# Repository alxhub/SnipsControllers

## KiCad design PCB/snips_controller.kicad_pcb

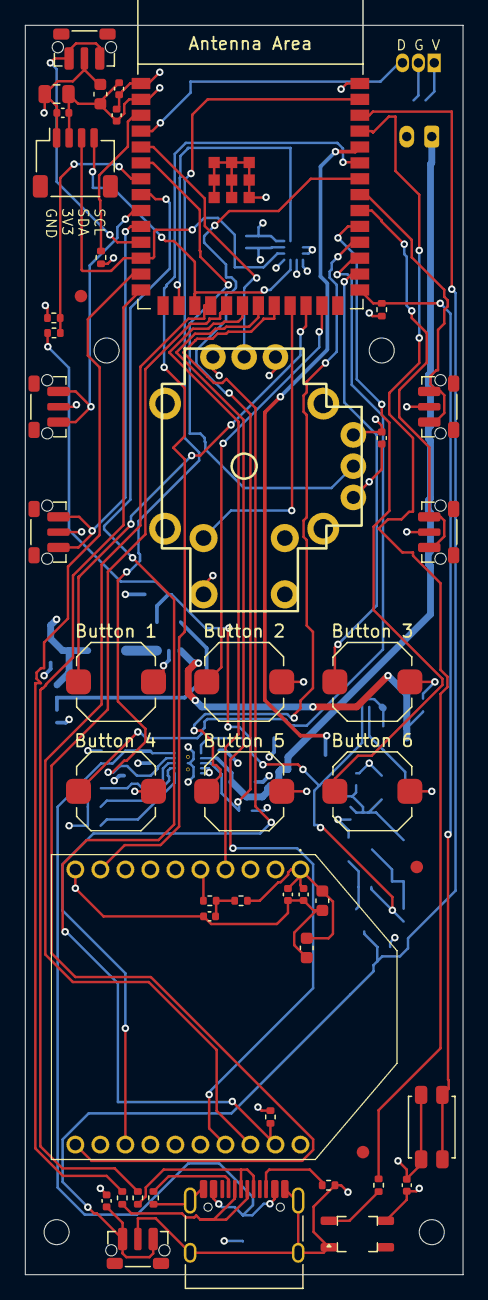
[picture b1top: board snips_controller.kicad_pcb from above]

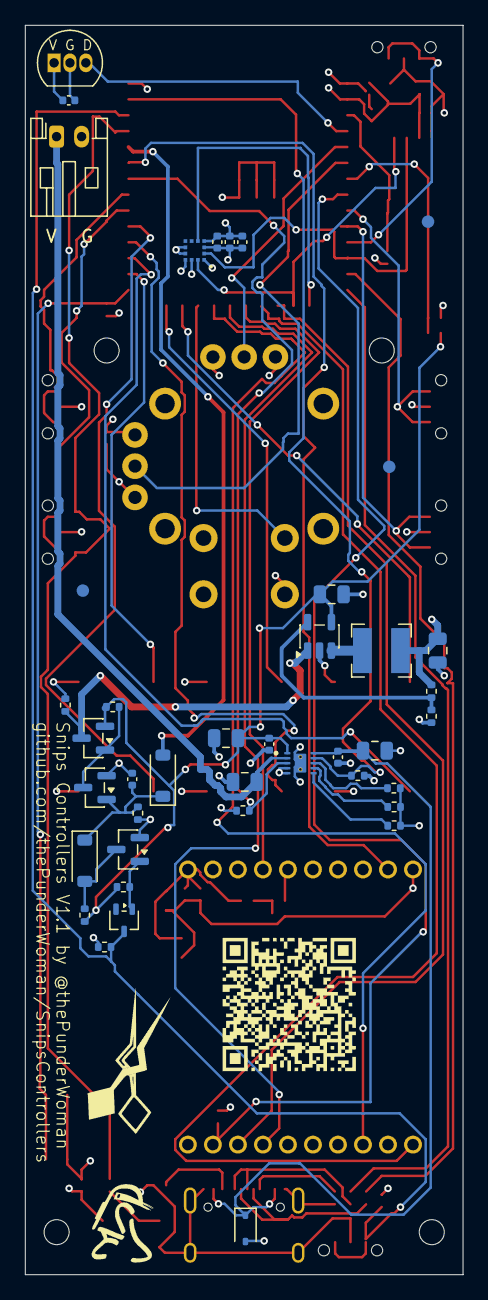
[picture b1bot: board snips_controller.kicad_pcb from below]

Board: 4 copper layers, 35.0 x 99.9 mm, 95 parts (44 on the bottom side), 57 nets.

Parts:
BT1: PH 2-pin battery RIGHT-ANGLE HORIZONTAL; JST_PH_S2B-PH-K_1x02_P2.00mm_Horizontal
C_3V3_1: 10µF; C_0603_1608Metric
C_3V3_2: 100nF; C_0402_1005Metric
C_3V3_3: 39pF; C_0402_1005Metric
C_ACCEL_1: 10nF; C_0402_1005Metric
C_ACCEL_2: 100pF; C_0402_1005Metric
C_ACCEL_3: 2.2nF; C_0402_1005Metric
C_BAT1: 10µF; C_0805_2012Metric
C_BUCK_IN1: 10µF; C_0805_2012Metric
C_BUCK_OUT1: 22µF; C_0805_2012Metric
C_DBNC1: 100nF; C_0402_1005Metric
C_HALL1: 100nF; C_0402_1005Metric
C_LATCH_G1: 100nF; C_0402_1005Metric
C_OLED_1: 10µF; C_0805_2012Metric
C_OLED_2: 100nF; C_0402_1005Metric
C_RGB1: 100nF; C_0402_1005Metric
C_STICK1: 100nF; C_0402_1005Metric
C_SYS_1: 10µF; C_0805_2012Metric
C_SYS_2: 100nF; C_0402_1005Metric
C_VIN_1: 10µF; C_0805_2012Metric
C_VIN_2: 100nF; C_0402_1005Metric
C_XBEE_RC1: 100nF; C_0402_1005Metric
C_XBEE_VCC1: 100nF; C_0402_1005Metric
C_XBEE_VCC2: 1µF; C_0603_1608Metric
C_XBEE_VCC3: 47pF; C_0402_1005Metric
C_XBEE_VCC4: 10µF; C_0603_1608Metric
D_INV_ISO1: BAT54W-7-F; SOT-323_SC-70
D_OR1, D_OR2: 1N4148W; D_SOD-123
D_RGB1: SK6812MINI-E-012
D_VBUS_TVS1: TPPESD5V0S1BA; D_SOD-323
FID1, FID2, FID3, FID4, FID5, FID6: Fiducial_1mm_Mask2mm
J_STICK1: GuliKit_Thumbstick; GuliKit_HallStick
J_USB1: USB-C; USB_C_Receptacle_HRO_TYPE-C-31-M-12
LOGO1, LOGO2: LOGO
LOGO3: LOGO; R2Builders
L_BUCK1: 2.2µH; L_Bourns-SRN4018
MH1, MH2, MH3, MH4: MountingHole_2mm
Q_INV1: MMBT3904(RANGE:100-300); SOT-23
Q_LATCH1: AO3400A; SOT-23
Q_PWR1: AO3401A; SOT-23
R_BOOT_PU1: 10kΩ; R_0402_1005Metric
R_BTN_PU1: 100kΩ; R_0402_1005Metric
R_CC1, R_CC2: 5.1kΩ; R_0402_1005Metric
R_EN_PU1: 10kΩ; R_0402_1005Metric
R_FB1: 255kΩ; R_0402_1005Metric
R_FB2: 56.2kΩ; R_0402_1005Metric
R_GATE1: 100kΩ; R_0402_1005Metric
R_INV_BASE1: 100kΩ; R_0402_1005Metric
R_INV_PU1: 100kΩ; R_0402_1005Metric
R_ISET1: 604Ω; R_0402_1005Metric
R_LATCH_G1: 1MΩ; R_0402_1005Metric
R_PWR_EN_PD1: 100kΩ; R_0402_1005Metric
R_RGB1: 470Ω; R_0402_1005Metric
R_STAT1, R_STAT2: 10kΩ; R_0402_1005Metric
R_TS1: 10kΩ; R_0402_1005Metric
R_USB_DM1: 27Ω; R_0402_1005Metric
R_USB_DP1: 27Ω; R_0402_1005Metric
R_VSET1: 18kΩ; R_0402_1005Metric
R_VSYS1: 200kΩ; R_0402_1005Metric
R_VSYS2: 100kΩ; R_0402_1005Metric
R_XBEE_ATTN_PU1: 10kΩ; R_0402_1005Metric
R_XBEE_RC1: 100Ω; R_0402_1005Metric
R_XBEE_RST1: 10kΩ; R_0402_1005Metric
SW_BOOT1: Panasonic_EVQP2; SW_SPST_EVQP2_ShortPushTravel_H2.1mm
SW_MACRO1, SW_MACRO2, SW_MACRO3, SW_MACRO4, SW_MACRO5, SW_MACRO6: 6x6x5mm SMD Tactile; SW_Push_1TS009xxxx-xxxx-xxxx_6x6x5mm
SW_PWR1: SKRTLAE010; SW_Push_1P1T-MP_NO_Horizontal_Alps_SKRTLAE010
SW_THR_DN1: SKRTLAE010; SW_Push_1P1T-MP_NO_Horizontal_Alps_SKRTLAE010
SW_THR_UP1: SKRTLAE010; SW_Push_1P1T-MP_NO_Horizontal_Alps_SKRTLAE010
SW_TRIG_DIG1: SKRTLAE010; SW_Push_1P1T-MP_NO_Horizontal_Alps_SKRTLAE010
SW_VOL_DN1: SKRTLAE010; SW_Push_1P1T-MP_NO_Horizontal_Alps_SKRTLAE010
SW_VOL_UP1: SKRTLAE010; SW_Push_1P1T-MP_NO_Horizontal_Alps_SKRTLAE010
U_ACCEL1: QMA6100P
U_BUCK1: TLV62569DBVR; SOT-23-5
U_CHG1: BQ25185DLHR; IC_BQ25185DLHR
U_HALL1: DRV5055A2QLPGM; TO-92_Inline
U_MCU1: ESP32-S3-WROOM-1-N8; ESP32-S3-WROOM-1
U_OLED1: Qwiic connector; JST_SH_SM04B-SRSS-TB_1x04-1MP_P1.00mm_Horizontal
U_XBEE1: XBee3; XB324Z8UTJ

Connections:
3V3: C_3V3_1.1, C_3V3_2.1, C_3V3_3.1, C_ACCEL_1.1, C_ACCEL_2.1, C_ACCEL_3.1, C_BUCK_OUT1.1, C_HALL1.1, C_OLED_1.1, C_OLED_2.1, C_RGB1.1, C_STICK1.1, C_XBEE_VCC1.1, C_XBEE_VCC2.1, C_XBEE_VCC3.1, C_XBEE_VCC4.1, D_RGB1.3 (VDD), J_STICK1.3 (X_HI), J_STICK1.3' (Y_HI), L_BUCK1.2, R_BOOT_PU1.2, R_BTN_PU1.1, R_EN_PU1.2, R_FB1.2, R_STAT1.2, R_STAT2.2, R_XBEE_ATTN_PU1.1, R_XBEE_RST1.1, U_ACCEL1.3 (VDD), U_ACCEL1.10 (SENB), U_HALL1.1 (VCC), U_MCU1.2 (3V3), U_OLED1.2 (VCC), U_XBEE1.1 (VCC)
/Accelerometer/I2C_SCL: U_ACCEL1.12 (SCX), U_MCU1.17 (GPIO9/TOUCH9/ADC1_CH8/FSPIHD/SUBSPIHD), U_OLED1.4 (SCL)
/Accelerometer/I2C_SDA: U_ACCEL1.2 (SDX), U_MCU1.12 (GPIO8/TOUCH8/ADC1_CH7/SUBSPICS1), U_OLED1.3 (SDA)
/Buttons_Direct/BTN_MACRO1: SW_MACRO1.1, U_MCU1.24 (GPIO47/SPICLK_P/SUBSPICLK_P_DIFF)
/Buttons_Direct/BTN_MACRO2: SW_MACRO2.1, U_MCU1.25 (GPIO48/SPICLK_N/SUBSPICLK_N_DIFF)
/Buttons_Direct/BTN_MACRO3: SW_MACRO3.1, U_MCU1.28 (SPIIO6/GPIO35/FSPID/SUBSPID)
/Buttons_Direct/BTN_MACRO4: SW_MACRO4.1, U_MCU1.29 (SPIIO7/GPIO36/FSPICLK/SUBSPICLK)
/Buttons_Direct/BTN_MACRO5: SW_MACRO5.1, U_MCU1.30 (SPIDQS/GPIO37/FSPIQ/SUBSPIQ)
/Buttons_Direct/BTN_MACRO6: SW_MACRO6.1, U_MCU1.31 (GPIO38/FSPIWP/SUBSPIWP)
/Buttons_Direct/BTN_THR_DN: SW_THR_DN1.1, U_MCU1.10 (GPIO17/U1TXD/ADC2_CH6)
/Buttons_Direct/BTN_THR_UP: SW_THR_UP1.1, U_MCU1.9 (GPIO16/U0CTS/ADC2_CH5/XTAL_32K_N)
/Buttons_Direct/BTN_TRIG_DIG: SW_TRIG_DIG1.1, U_MCU1.11 (GPIO18/U1RXD/ADC2_CH7/CLK_OUT3)
/Buttons_Direct/BTN_VOL_DN: SW_VOL_DN1.1, U_MCU1.32 (MTCK/GPIO39/CLK_OUT3/SUBSPICS1)
/Buttons_Direct/BTN_VOL_UP: SW_VOL_UP1.1, U_MCU1.33 (MTDO/GPIO40/CLK_OUT2)
/Hall_Trigger/TRIG_ANALOG: U_HALL1.3 (OUT), U_MCU1.4 (GPIO4/TOUCH4/ADC1_CH3)
/MCU_Core/BTN_STICK: J_STICK1.a (SW_A), U_MCU1.23 (GPIO21)
/MCU_Core/MCU_BOOT: R_BOOT_PU1.1, SW_BOOT1.2, U_MCU1.27 (GPIO0/BOOT)
/MCU_Core/MCU_EN: R_EN_PU1.1, U_MCU1.3 (EN)
/MCU_Core/PWR_BTN_SENSE: C_DBNC1.1, D_INV_ISO1.3 (K), R_BTN_PU1.2, SW_PWR1.1, U_MCU1.38 (GPIO2/TOUCH2/ADC1_CH1)
/MCU_Core/PWR_HOLD: D_OR2.2 (A), U_MCU1.36 (U0RXD/GPIO44/CLK_OUT2)
/MCU_Core/RGB_DIN: R_RGB1.2, U_MCU1.37 (U0TXD/GPIO43/CLK_OUT1)
/MCU_Core/SPI_MISO: U_MCU1.20 (GPIO12/TOUCH12/ADC2_CH1/FSPICLK/FSPIIO6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), U_XBEE1.4 (SPI_MISO)
/MCU_Core/SPI_MOSI: U_MCU1.19 (GPIO11/TOUCH11/ADC2_CH0/FSPID/FSPIIO5/S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), U_XBEE1.11 (SPI_MOSI)
/MCU_Core/SPI_SCK: U_MCU1.18 (GPIO10/TOUCH10/ADC1_CH9/FSPICS0/FSPIIO4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), U_XBEE1.18 (SPI_CLK)
/MCU_Core/STAT1: R_STAT1.1, U_CHG1.9 (STAT1), U_MCU1.39 (GPIO1/TOUCH1/ADC1_CH0)
/MCU_Core/STAT2: R_STAT2.1, U_CHG1.3 (STAT2), U_MCU1.34 (MTDI/GPIO41/CLK_OUT1)
/MCU_Core/STICK_X: J_STICK1.2 (X_OUT), U_MCU1.5 (GPIO5/TOUCH5/ADC1_CH4)
/MCU_Core/STICK_Y: J_STICK1.2' (Y_OUT), U_MCU1.6 (GPIO6/TOUCH6/ADC1_CH5)
/MCU_Core/USB_DM: J_USB1.A7 (D-), J_USB1.B7 (D-), R_USB_DM1.1
/MCU_Core/USB_DM_MCU: R_USB_DM1.2, U_MCU1.13 (GPIO19/U1RTS/ADC2_CH8/CLK_OUT2/USB_D-)
/MCU_Core/USB_DP: J_USB1.A6 (D+), J_USB1.B6 (D+), R_USB_DP1.1
/MCU_Core/USB_DP_MCU: R_USB_DP1.2, U_MCU1.14 (GPIO20/U1CTS/ADC2_CH9/CLK_OUT1/USB_D+)
/MCU_Core/VSYS_SENSE: R_VSYS1.2, R_VSYS2.1, U_MCU1.7 (GPIO7/TOUCH7/ADC1_CH6)
/MCU_Core/XBEE_ON_SLEEP: U_MCU1.22 (GPIO14/TOUCH14/ADC2_CH3/FSPIWP/FSPIDQS/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), U_XBEE1.13 (ON_SLEEP)
/MCU_Core/XBee_CS: U_MCU1.21 (GPIO13/TOUCH13/ADC2_CH2/FSPIQ/FSPIIO7/S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), U_XBEE1.17 (SPI_SSEL)
/Power_Buck/BUCK_FB: R_FB1.1, R_FB2.1, U_BUCK1.5 (FB)
/Power_Buck/BUCK_SW: L_BUCK1.1, U_BUCK1.3 (SW)
/Power_Buck/PWR_EN: Q_PWR1.3 (D), R_PWR_EN_PD1.1, U_BUCK1.1 (EN)
/Power_Charger/CHG_ISET: R_ISET1.1, U_CHG1.8 (ISET)
/Power_Charger/CHG_TS: R_TS1.1, U_CHG1.6 (TS/MR)
/Power_Charger/CHG_VSET: R_VSET1.1, U_CHG1.7 (ILIM/VSET)
/Power_Control/PWR_BTN_INV_BASE: D_INV_ISO1.1 (A), Q_INV1.1 (B), R_INV_BASE1.2
/Power_Control/PWR_BTN_TRIGGER: D_OR1.2 (A), Q_INV1.3 (C), R_INV_PU1.2
/Power_Control/PWR_GATE: Q_LATCH1.3 (D), Q_PWR1.1 (G), R_GATE1.2
/Power_Control/PWR_LATCH_G: C_LATCH_G1.2, D_OR1.1 (K), D_OR2.1 (K), Q_LATCH1.1 (G), R_LATCH_G1.2
/RGB_LED/RGB_DIN_R: D_RGB1.2 (DIN), R_RGB1.1
/USB_C/USB_CC1: J_USB1.A5 (CC1), R_CC1.1
/USB_C/USB_CC2: J_USB1.B5 (CC2), R_CC2.1
/XBee/XBEE_RESET: R_XBEE_RC1.2, U_XBEE1.5 (RESET)
/XBee/XBEE_RST_PU: C_XBEE_RC1.1, R_XBEE_RC1.1, R_XBEE_RST1.2
/XBee/XBEE_SPI_ATTN: R_XBEE_ATTN_PU1.2, U_MCU1.8 (GPIO15/U0RTS/ADC2_CH4/XTAL_32K_P), U_XBEE1.19 (SPI_ATTN)
ACCEL_INT1: U_ACCEL1.5 (INT1), U_MCU1.16 (GPIO46)
GND: BT1.2, C_3V3_1.2, C_3V3_2.2, C_3V3_3.2, C_ACCEL_1.2, C_ACCEL_2.2, C_ACCEL_3.2, C_BAT1.2, C_BUCK_IN1.2, C_BUCK_OUT1.2, C_DBNC1.2, C_HALL1.2, C_LATCH_G1.1, C_OLED_1.2, C_OLED_2.2, C_RGB1.2, C_STICK1.2, C_SYS_1.2, C_SYS_2.2, C_VIN_1.2, C_VIN_2.2, C_XBEE_RC1.2, C_XBEE_VCC1.2, C_XBEE_VCC2.2, C_XBEE_VCC3.2, C_XBEE_VCC4.2, D_RGB1.1 (VSS), D_VBUS_TVS1.2 (A2), J_STICK1.1 (X_LO), J_STICK1.1' (Y_LO), J_STICK1.c (SW_C), J_USB1.A1 (GND), J_USB1.A12 (GND), J_USB1.B1 (GND), J_USB1.B12 (GND), J_USB1.SH (SHIELD), Q_INV1.2 (E), Q_LATCH1.2 (S), R_CC1.2, R_CC2.2, R_FB2.2, R_ISET1.2, R_LATCH_G1.1, R_PWR_EN_PD1.2, R_TS1.2, R_VSET1.2, R_VSYS2.2, SW_BOOT1.1, SW_MACRO1.2, SW_MACRO2.2, SW_MACRO3.2, SW_MACRO4.2, SW_MACRO5.2, SW_MACRO6.2, SW_PWR1.2, SW_THR_DN1.2, SW_THR_UP1.2, SW_TRIG_DIG1.2, SW_VOL_DN1.2, SW_VOL_UP1.2, U_ACCEL1.1 (AD0), U_ACCEL1.4 (RESV1), U_ACCEL1.8 (GNDIO), U_ACCEL1.9 (GND), U_ACCEL1.11 (RESV2), U_BUCK1.2 (GND), U_CHG1.4 (~CE), U_CHG1.5 (GND), U_CHG1.11 (THERMAL_PAD), U_CHG1.12, U_CHG1.13, U_HALL1.2 (GND), U_MCU1.1 (GND), U_MCU1.40 (GND), U_MCU1.41 (GND), U_OLED1.1 (GND), U_XBEE1.10 (GND)
VBAT: BT1.1, C_BAT1.1, U_CHG1.2 (BAT)
VBUS: C_VIN_1.1, C_VIN_2.1, D_VBUS_TVS1.1 (A1), J_USB1.A4 (VBUS), J_USB1.A9 (VBUS), J_USB1.B4 (VBUS), J_USB1.B9 (VBUS), U_CHG1.10 (IN)
VSYS: C_BUCK_IN1.1, C_SYS_1.1, C_SYS_2.1, Q_PWR1.2 (S), R_GATE1.1, R_INV_BASE1.1, R_INV_PU1.1, R_VSYS1.1, U_BUCK1.4 (VIN), U_CHG1.1 (SYS)
XBEE_SLEEP_RQ: U_MCU1.35 (MTMS/GPIO42), U_XBEE1.9 (DTR)

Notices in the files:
parts and their libraries:
Adapted from dbenoy/thumbstick-breakout (CC-BY-SA 4.0, Copyright (c) Daniel Benoy), which itself used the C&K THB001P datasheet for dimensions.
Adapted from dbenoy/thumbstick-breakout (CC-BY-SA 4.0, Copyright (c) Daniel Benoy).
